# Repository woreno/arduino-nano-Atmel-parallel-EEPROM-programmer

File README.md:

# arduino-nano-eeprom-programmer
Atmel AT28C64/128/256 parallel EEPROMs programmer using Arduino Nano Every

This gadget was from 2020. I tried to build a board following Ben Eater's schematic, for accepting different sizes of parallel EEPROMS using switches. After i realized that some EEPROMs i bought in AliExpress had Software Data Protection (SDP), so i needed to add code to unblock these. However some failed to unprotect using this method (because the filling the serial register takes times), so i had to use a larger GPIO, Arduino Uno, to unblock them using all the GPIO in parallel. These protected PROMs need faster speeds for
unprotect (see the correct timmings in Atmel datasheets - SDP applies only, i believe, to the 256 and beyond chips).

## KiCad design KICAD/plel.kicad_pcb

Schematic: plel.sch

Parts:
C1: C; standard_2pins_half
R1, R2, R3, R4, R5: R; standard_2pins
U1, U3: 74HC595; standard_DIP_16Pins
U2: ArduinoNano; Arduino_Nano
U4, U5, U6, U7, U8, U9, U10, U11: flipSwitch; mini_flipswitch2.54
Z1: ZIFsocket20_Memory; ZIF socket

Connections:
+5V: R1.1, R2.1, R3.1, R4.1, R5.1, U1.16 (VCC), U3.16 (VCC), U11.1 (line1)
/A0: U3.6 (QG), Z1.12 (A0)
/A1: U3.5 (QF), Z1.11 (A1)
/A2: U3.4 (QE), Z1.10 (A2)
/A3: U3.3 (QD), Z1.9 (A3)
/A4: U3.2 (QC), Z1.8 (A4)
/A5: U3.1 (QB), Z1.7 (A5)
/A6: U3.15 (QA), Z1.6 (A6)
/A7: U1.7 (QH), Z1.5 (A7)
/A8: U1.6 (QG), Z1.35 (A8)
/A9: U1.5 (QF), Z1.34 (A9)
/A10: U1.4 (QE), Z1.31 (A10)
/A11: U1.3 (QD), Z1.33 (A11)
/A12: U1.2 (QC), Z1.4 (A12)
/A13: U1.1 (QB), Z1.36 (A13///NC)
/A14: U1.15 (QA), U5.1 (line1), U7.3 (line2)
/CLOCK_SHIFT: U1.11 (SRCLK), U2.21, U3.11 (SRCLK)
/CLOCK_STORE: U1.12 (RCLK), U2.22, U3.12 (RCLK)
/D0: U2.23, Z1.13 (D0), Z1.19, Z1.22
/D1: U2.24, Z1.14 (D1), Z1.18, Z1.23
/D2: U2.25, Z1.15 (D2), Z1.24
/D3: U2.26, Z1.25 (D3)
/D4: U2.27, Z1.26 (D4)
/D5: U2.28, Z1.27 (D5)
/D6: U2.29, Z1.28 (D6)
/D7: U2.30, Z1.29 (D7)
/MEMPOWER: C1.2, U8.3 (line2), U11.2 (short), Z1.40 (VCC/NC)
/SERIAL_DATA: U1.14 (SER), U2.20
/~OE: U3.7 (QH), Z1.32 (~OE)
/~WE: U2.1, U7.1 (line1), Z1.39 (~WE/NC)
GND: C1.1, U1.8 (GND), U1.13 (~OE), U2.14, U3.8 (GND), U3.13 (~OE), U4.1 (line1), U6.1 (line1), U9.1 (line1), U11.3 (line2), Z1.16 (GND), Z1.30 (~CE)
unnamed: R1.2, U3.10 (~SRCLR)
unnamed: R2.2, U1.10 (~SRCLR)
unnamed: R3.2, U4.3 (line2)
unnamed: R4.2, U6.3 (line2)
unnamed: R5.2, U9.3 (line2)
unnamed: U1.9 (QH'), U3.14 (SER)
unnamed: U4.2 (short), U5.3 (line2)
unnamed: U5.2 (short), Z1.3 (A15/A14/NC)
unnamed: U6.2 (short), Z1.2 (A16/NC)
unnamed: U7.2 (short), Z1.37 (A14/~WE)
unnamed: U8.1 (line1), U9.2 (short)
unnamed: U8.2 (short), Z1.38 (A17/NC/VCC)
unnamed: U2.17, U10.2 (short)
unnamed: U2.16, U10.3 (line2)

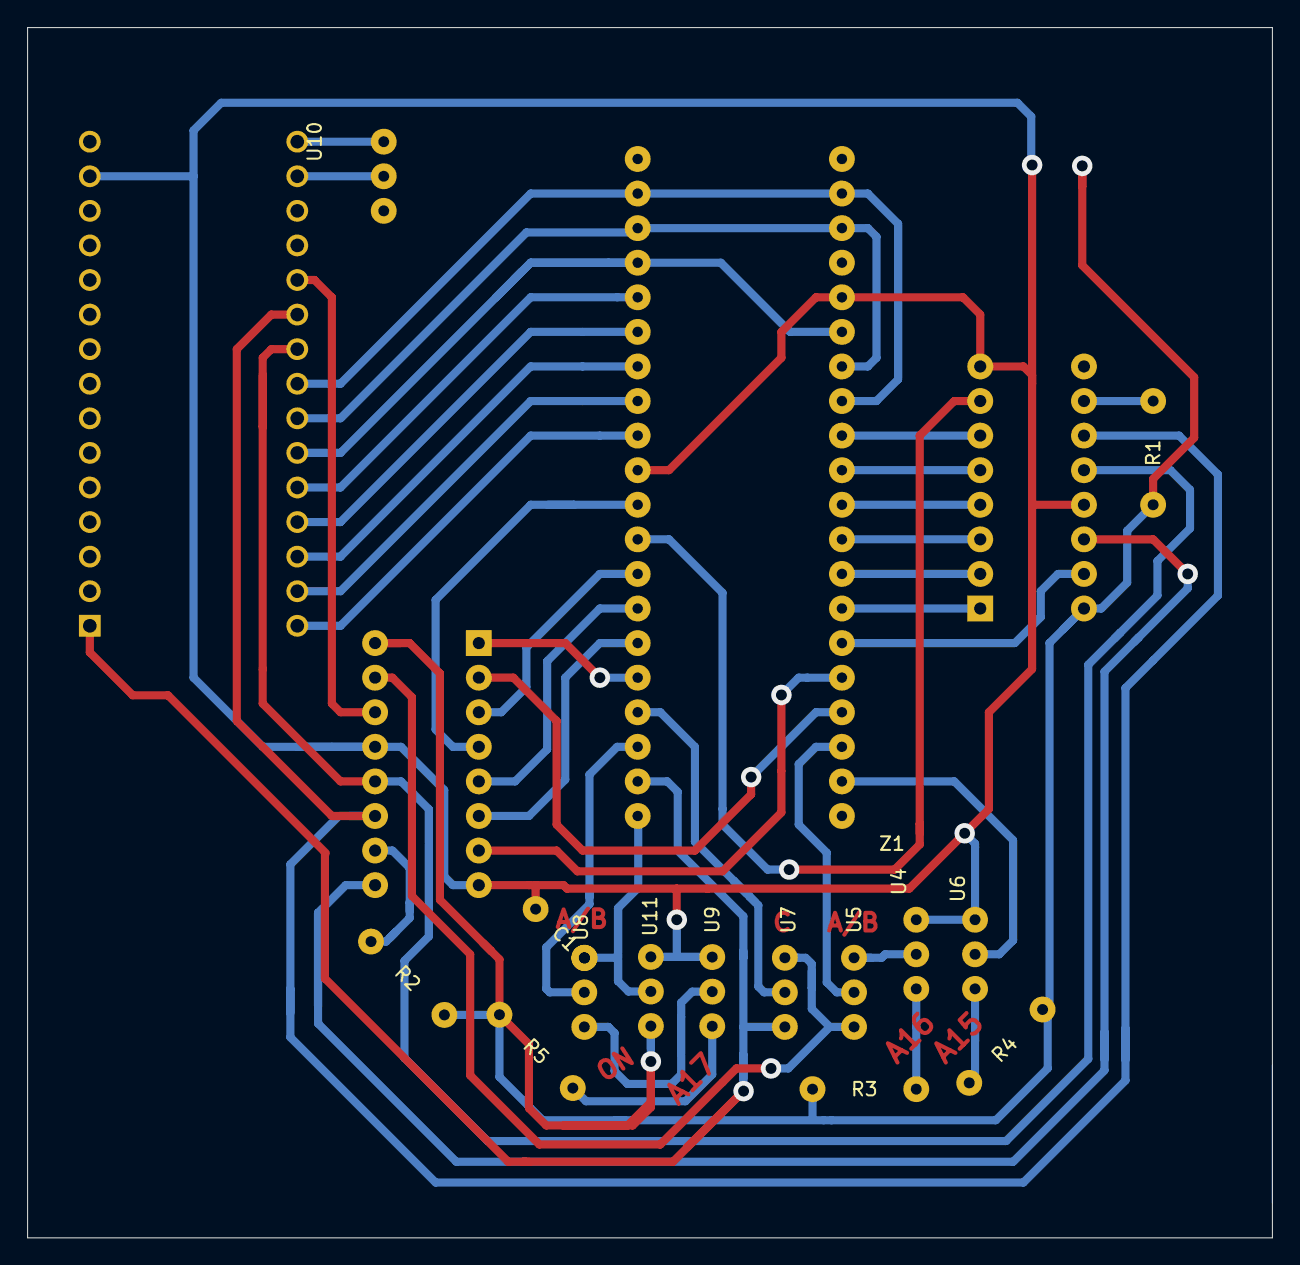
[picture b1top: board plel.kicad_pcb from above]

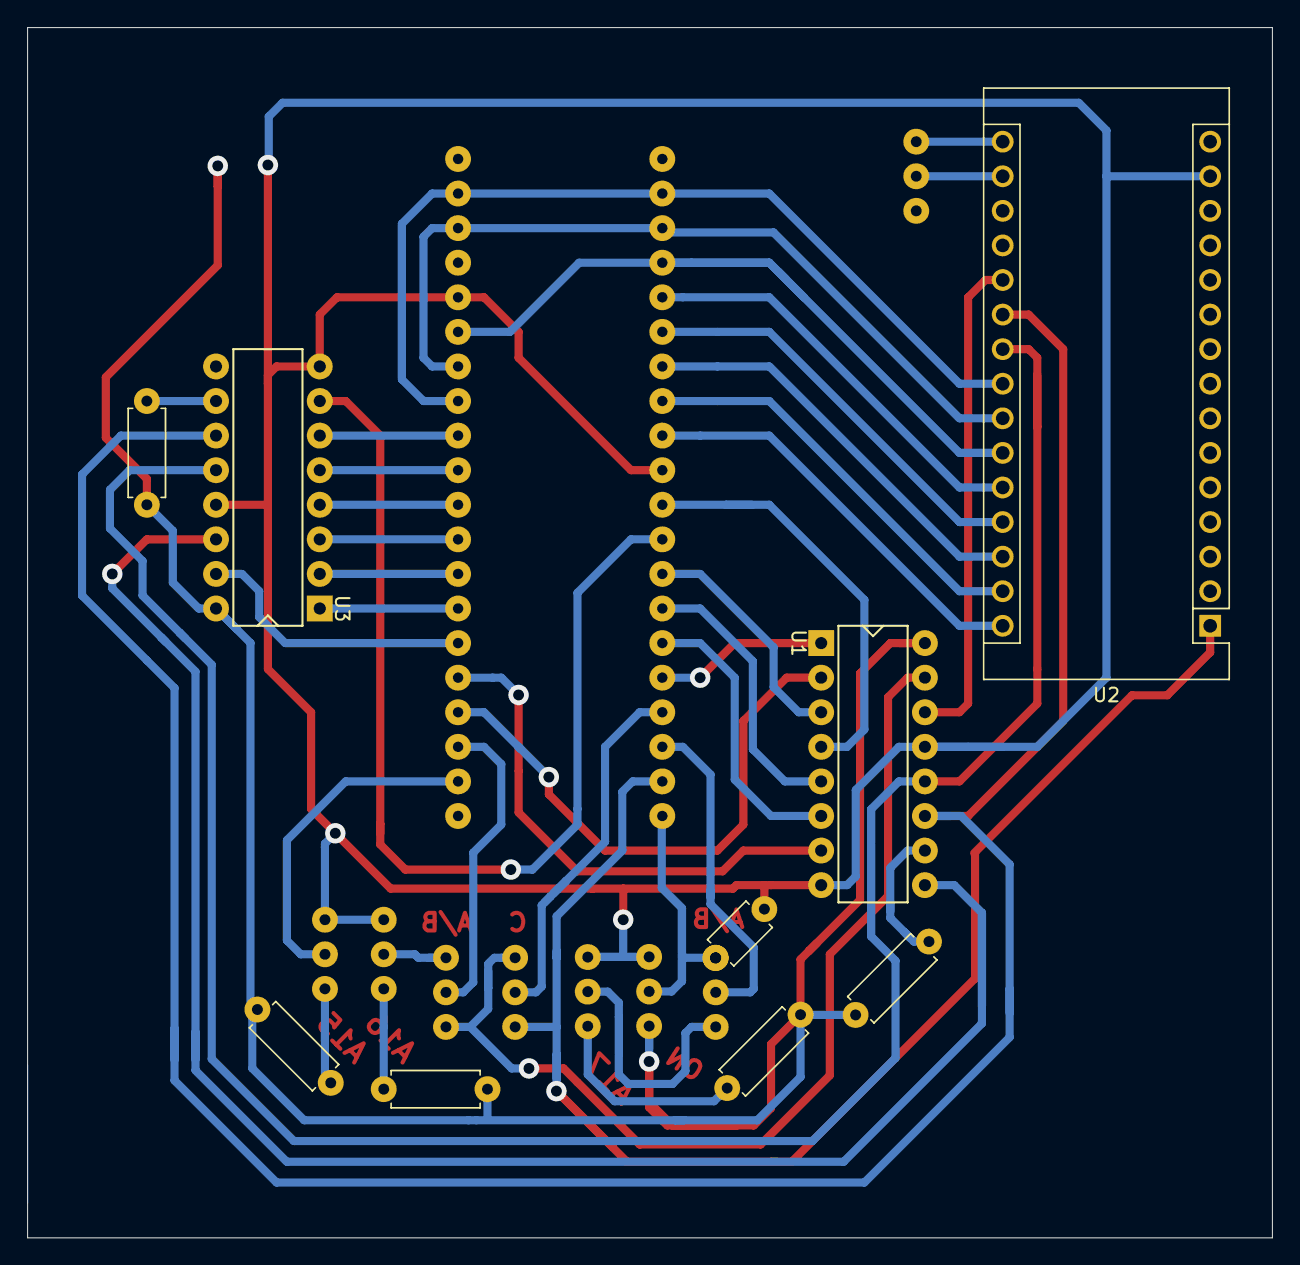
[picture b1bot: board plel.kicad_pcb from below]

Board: 2 copper layers, 91.4 x 88.9 mm, 18 parts (3 on the bottom side), 45 nets.
